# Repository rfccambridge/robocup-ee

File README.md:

## Installing ROS Kinetic
- Follow the steps 1.1 - 1.5 in this guide here: http://wiki.ros.org/kinetic/Installation/Ubuntu

## Build Environment Installation

- Make sure you have clang-format installed: 

        apt-cache search clang-format
        sudo apt-get install clang-format-<version>
    
- `source /opt/ros/kinetic/setup.bash`
- `cd <your robocup directory>/catkin_ws/src`
- `catkin_init_workspace`
- `cd <your robocup directory>/catkin_ws`
- `catkin_make`
- `rosrun using_markers brain`
- `source <your robocup directory>/catkin_ws/devel/setup.bash`

### Persistent Evinvironment Setup
- To have ROS initialized everytime you open a terminal window, simply add the `source` line above to the end of your `~/.bashrc` file.

## Running the Rendered, Simulator and Engine
### Renderer
- `roscore`
- `rosrun rviz rviz`

### Simulator
- `rosrun using_markers simulator`

### Engine
- Make sure running `echo $ROS_PACKAGE_PATH` prints something similar to `/home/<your_user>/catkin_ws/src:/opt/ros/kinetic/share:/opt/ros/kinetic/stacks`

## Setting Up Your Own Branch To Work In

- `git checkout -b <your name>_branch`
- Now, all changes you make will affect only your environment and no one else's.

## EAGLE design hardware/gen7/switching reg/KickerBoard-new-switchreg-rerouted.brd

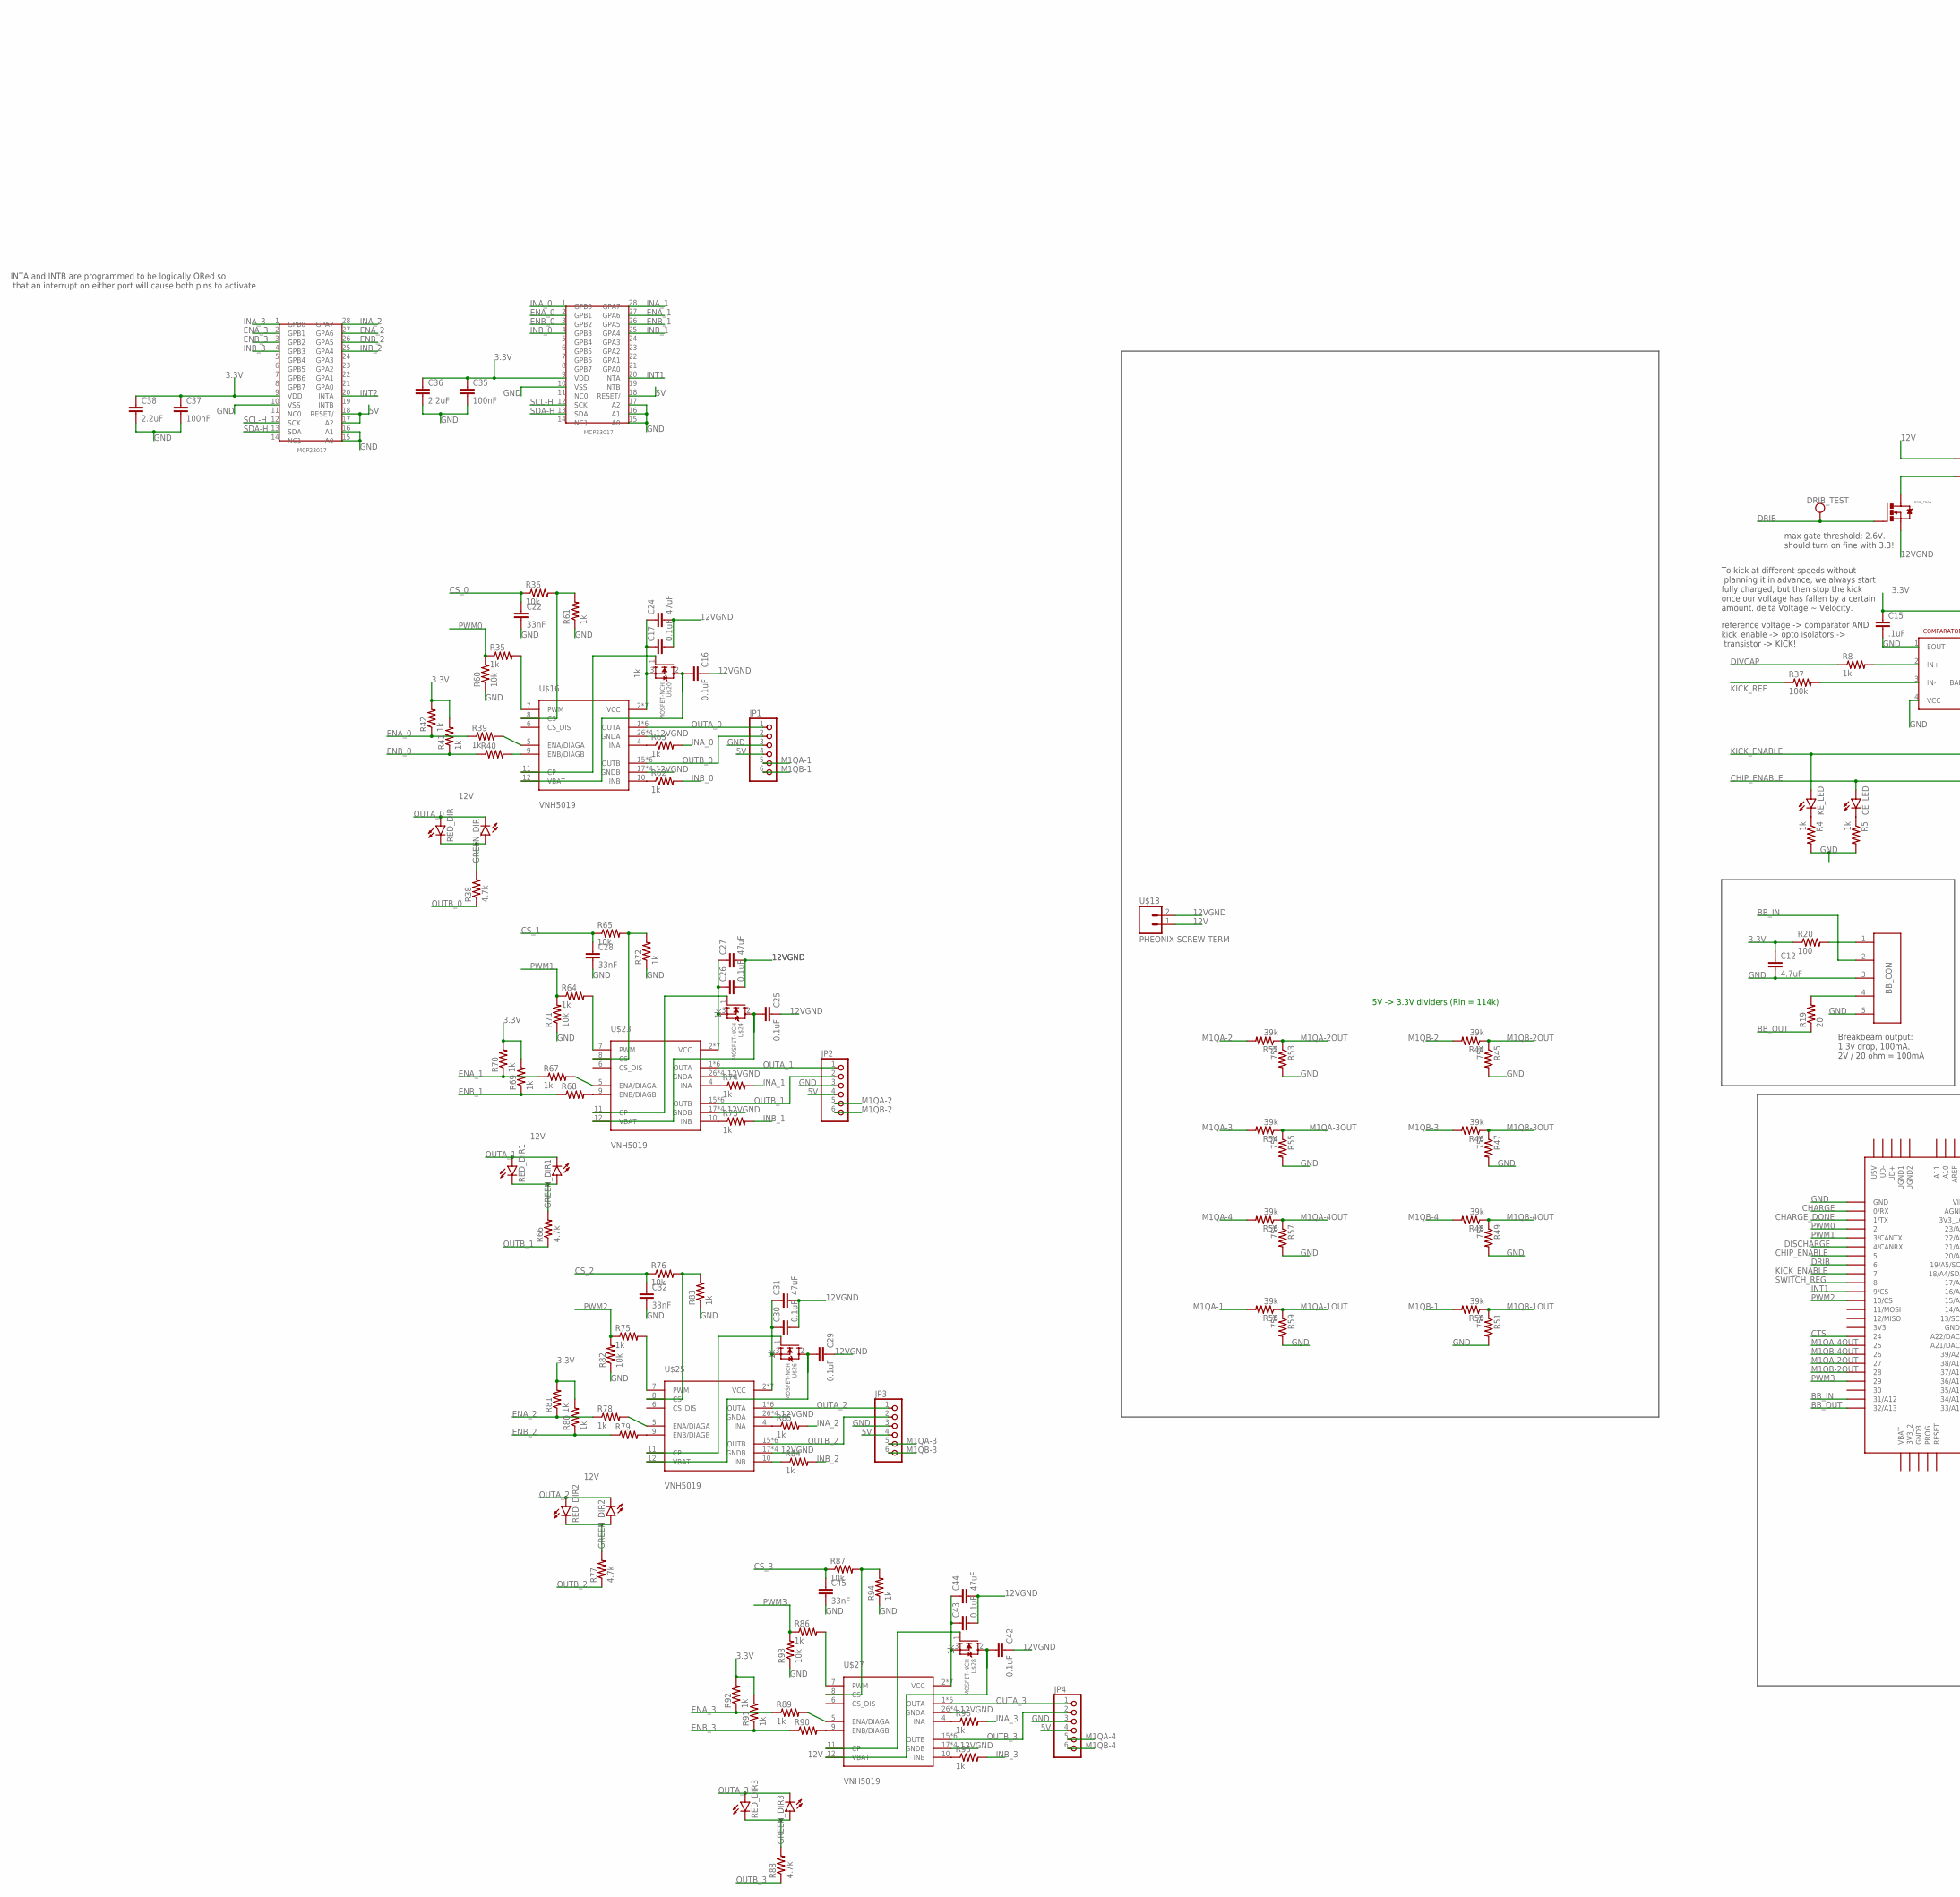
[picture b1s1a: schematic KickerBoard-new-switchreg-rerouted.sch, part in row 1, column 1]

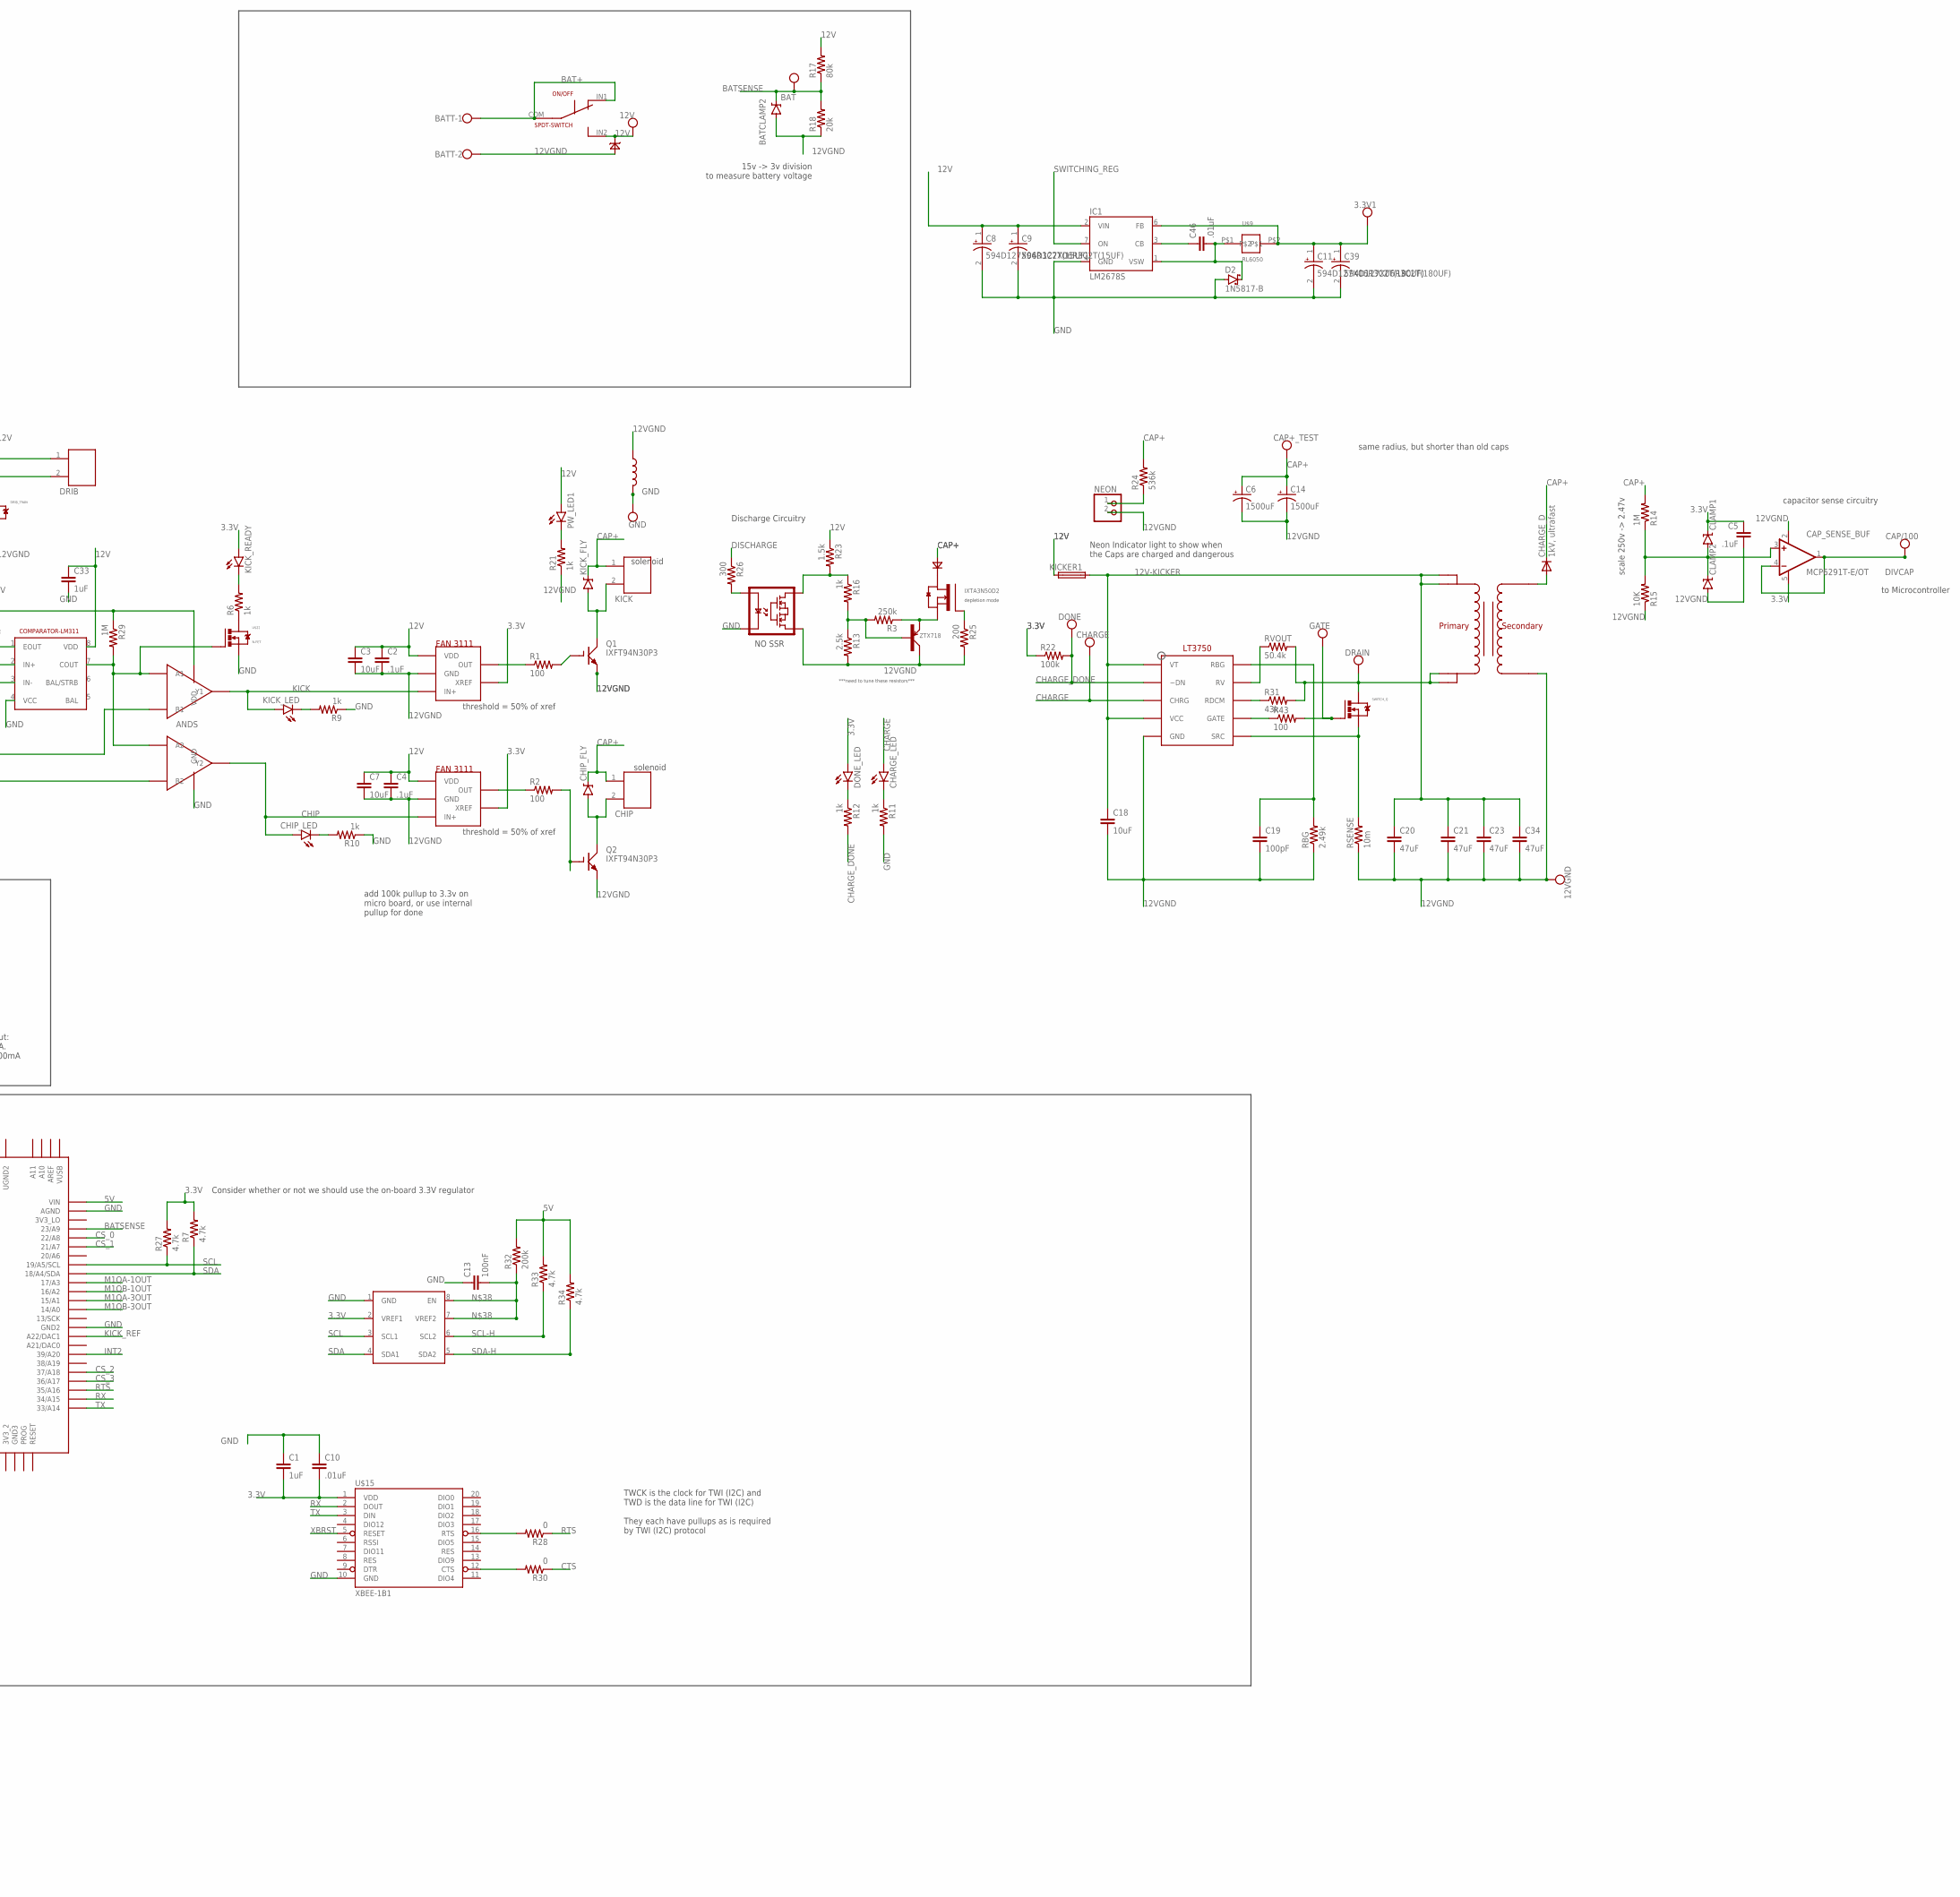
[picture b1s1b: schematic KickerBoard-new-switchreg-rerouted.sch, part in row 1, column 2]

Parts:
3.3V1, 12V, 12VGND: TEST_PT; TESTING_PT
ANDS: AND-DUAL; TSSOP8
BAT: TEST_PT; TESTING_PT
BATCLAMP2: DIODE-ZENERDO214AC; DO214AC
BATT: W237-102
BB_CON: JST-5; JST-5-2MM
C1, C33: 1uF; 1206
C2, C4: .1uF; 1206
C3, C7: 10uF; 1206
C5, C15: .1uF; 0805
C6, C14: 1500uF; EB35D
C8, C9: 594D127X06R3C2T(15UF); CAPCP7132X250N
C10: .01uF; 1206
C11, C39: 594D127X06R3C2T(180UF); CAPCP7132X250N
C12: 4.7uF; 0805
C13, C35, C37: 100nF; 0805
C16, C17, C25, C26, C29, C30, C42, C43: 0.1uF; 0805
C18: 10uF; 0805
C19: 100pF; 0805
C20, C21, C23, C24, C27, C31, C34, C44: 47uF; 1206
C22, C28, C32, C45: 33nF; 0805
C36, C38: 2.2uF; 0805
C46: .01uF; 0805
CAP+_TEST: TEST_PT; TESTING_PT
CAP/100: TEST_PT; TESTING_PT
CAP_SENSE_BUF: MCP6291T-E/OT; SOT23-5
CE_LED: LED1206; LED-1206
CHARGE: TEST_PT; TESTING_PT
CHARGE_D: 1kV, ultrafast; DO214AC
CHARGE_LED: LED1206; LED-1206
CHARGE_U: LT3750; 10-MSOP
CHIP: JST-22MM; JST-2-2MM
CHIP_FLY: DIODE-ZENERDO214AB; DO214AB
CHIP_LED: LED1206; LED-1206
CLAMP1, CLAMP2: DIODE-ZENERDO214AC; DO214AC
D2: 1N5817-B; DO41-7.6
DONE: TEST_PT; TESTING_PT
DONE_LED: LED1206; LED-1206
DRAIN: TEST_PT; TESTING_PT
DRIB: JST-22MM; JST-2-2MM
DRIB_TEST: TEST_PT; TESTING_PT
DRIB_TRAN: N-MOSFETDPAK; DPAK
GATE: TEST_PT; TESTING_PT
GND: TEST_PT; TESTING_PT
GREEN_DIR, GREEN_DIR1, GREEN_DIR2, GREEN_DIR3: LED1206; LED-1206
IC1: LM2678S; TO263-7
JP1, JP2, JP3, JP4: PINHD-1X6; 1X06
KE_LED: LED1206; LED-1206
KICK: JST-22MM; JST-2-2MM
KICKER1: TR5
KICK_FLY: DIODE-ZENERDO214AB; DO214AB
KICK_LED: LED1206; LED-1206
KICK_READY: LED1206; LED-1206
NEON: PINHD-1X2; 1X02
ON/OFF: SPDT-SWITCH; CK_SWITCH
PW_LED1: LED1206; LED-1206
Q1, Q2: IXFT94N30P3; TO268
R1, R2, R20, R43: 100; 0805
R3: 250k; 0805
R4, R5, R6, R8, R9, R10, R11, R12, R16, R21, R35, R39, R40, R41, R42, R61, R62, R63, R64, R67, R68, R69, R70, R72, R73, R74, R75, R78, R79, R80, R81, R83, R84, R85, R86, R89, R90, R91, R92, R94, R95, R96: 1k; 0805
R7, R27, R33, R34, R38, R66, R77, R88: 4.7k; 0805
R13: 2.5k; 0805
R14, R29: 1M; 0805
R15: 10K; 0805
R17: 80k; 0805
R18: 20k; 0805
R19: 20; 0805
R22, R37: 100k; 0805
R23: 1.5k; 0805
R24: 536k; 0805
R25: 200; 0805
R26: 300; 0805
R28, R30: 0; 0805
R31: 43k; 0805
R32: 200k; 0805
R36, R60, R65, R71, R76, R82, R87, R93: 10k; 0805
R44, R46, R48, R50, R52, R54, R56, R58: 39k; 0805
R45, R47, R49, R51, R53, R55, R57, R59: 75k; 0805
RBG: 2.49k; 0805
RED_DIR, RED_DIR1, RED_DIR2, RED_DIR3: LED1206; LED-1206
RSENSE: 10m; R2512
RVOUT: 50.4k; 0805
SWITCH_Q: N-MOSFETDPAK; DPAK
U$1, U$4: FAN31111; SOT23-5
U$2: IXTA3N50D2; TO-263
U$3: 32052-TRANSFORMER; 10-TRANSFORMER
U$5: VO1400AEFTR; SOP4
U$6: ZTX718; TO92
U$7: 1N4007; THROUGH-HOLE-2
U$8: PCA9306; SOIC8
U$9: RL6050
U$12: 13VZENER; THROUGH-HOLE-2
U$13: PHEONIX-SCREW-TERM; 1X02-PHEONIX
U$14: TEENSY_3.5/3.6
U$15: XBEE-1B1; XBEE-1
U$16, U$23, U$25, U$27: VNH5019; MULTIPOWERSO-30
U$17, U$21: IO-EXPANDER; SSOP
U$18: LM311; SOIC8
U$19: INDUCTOR; 0805
U$20, U$24, U$26, U$28: MOSFET-NCH; TO252-3
U$22: N-FET; SOT-23

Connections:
3.3V: ANDS.P$8 (VDD), C1.2, C5.1, C10.2, C12.1, C15.1, C35.1, C36.1, C37.1, C38.1, CAP_SENSE_BUF.5 (V+), CLAMP1.C, DONE_LED.A, KICK_READY.A, R7.2, R20.1, R22.1, R27.2, R29.1, R41.2, R42.2, R69.2, R70.2, R80.2, R81.2, R91.2, R92.2, U$1.4 (XREF), U$4.4 (XREF), U$8.2 (VREF1), U$15.1 (VDD), U$17.9 (VDD), U$21.9 (VDD)
5V: JP1.4, JP2.4, JP3.4, JP4.4, R32.2, R33.2, R34.2, U$14.VIN, U$17.18 (RESET/), U$21.17 (A2), U$21.18 (RESET/)
12V: 12V.P$1, C2.1, C3.1, C4.1, C7.1, C8.1, C9.1, C16.1, C25.1, C29.1, C33.1, C42.1, DRIB.1, IC1.2 (VIN), KICKER1.1, ON/OFF.IN2 (P2), PW_LED1.A, R17.2, R23.1, U$1.1 (VDD), U$4.1 (VDD), U$12.-, U$13.1, U$16.12 (VBAT), U$18.8 (VDD), U$20.2 (D), U$23.12 (VBAT), U$24.2 (D), U$25.12 (VBAT), U$26.2 (D), U$27.12 (VBAT), U$28.2 (D)
12V-KICKER: C18.1, C20.1, C21.1, C23.1, C34.1, CHARGE_U.P$1 (VT), CHARGE_U.P$4 (VCC), KICKER1.2, U$3.P$4, U$3.P$5
12VGND: 12VGND.P$1, BATCLAMP2.A, BATT.2, C2.2, C3.2, C4.2, C5.2, C6.-, C7.2, C14.-, C16.2, C17.2, C18.2, C19.2, C20.2, C21.2, C23.2, C24.2, C25.2, C26.2, C27.2, C29.2, C30.2, C31.2, C34.2, C42.2, C43.2, C44.2, CAP_SENSE_BUF.2 (V-), CHARGE_U.P$5 (GND), CLAMP2.A, DRIB_TRAN.SOURCE (S), NEON.2, Q1.E, Q2.E, R13.2, R15.1, R18.1, R21.1, R25.2, RBG.1, RSENSE.1, U$1.2 (GND), U$3.P$10, U$4.2 (GND), U$5.3 (S2), U$6.LEFT (COLLECTOR), U$12.+, U$13.2, U$16.17 (GNDB), U$16.18 (GNDB), U$16.19 (GNDB), U$16.20 (GNDB), U$16.26 (GNDA), U$16.27 (GNDA), U$16.28 (GNDA), U$16.29 (GNDA), U$19.1, U$23.17 (GNDB), U$23.18 (GNDB), U$23.19 (GNDB), U$23.20 (GNDB), U$23.26 (GNDA), U$23.27 (GNDA), U$23.28 (GNDA), U$23.29 (GNDA), U$25.17 (GNDB), U$25.18 (GNDB), U$25.19 (GNDB), U$25.20 (GNDB), U$25.26 (GNDA), U$25.27 (GNDA), U$25.28 (GNDA), U$25.29 (GNDA), U$27.17 (GNDB), U$27.18 (GNDB), U$27.19 (GNDB), U$27.20 (GNDB), U$27.26 (GNDA), U$27.27 (GNDA), U$27.28 (GNDA), U$27.29 (GNDA)
BAT+: BATT.1, ON/OFF.COM, ON/OFF.IN1 (P1)
BATSENSE: BAT.P$1, BATCLAMP2.C, R17.1, R18.2, U$14.23/A9
BB_IN: BB_CON.2, U$14.31/A12
BB_OUT: R19.1, U$14.32/A13
CAP+: C6.+, C14.+, CAP+_TEST.P$1, CHARGE_D.C, CHIP.1, CHIP_FLY.CATHODE (C), KICK.1, KICK_FLY.CATHODE (C), R14.2, R24.2, U$7.+ (D+)
CHARGE: CHARGE.P$1, CHARGE_LED.A, CHARGE_U.P$3 (CHRG), U$14.0/RX
CHARGE_DONE: CHARGE_U.P$2 (~DN), DONE.P$1, R12.2, R22.2, U$14.1/TX
CHIP: ANDS.P$3 (Y2), CHIP_LED.A, U$1.3 (IN+)
CHIP_ENABLE: ANDS.P$6 (B2), CE_LED.A, U$14.5
COMP_OUT: ANDS.P$1 (A1), ANDS.P$5 (A2), R29.2, U$18.7 (COUT), U$22.G
CS_0: C22.1, R36.1, U$14.22/A8
CS_1: C28.1, R65.1, U$14.21/A7
CS_2: C32.1, R76.1, U$14.37/A18
CS_3: C45.1, R87.1, U$14.36/A17
CTS: R30.1, U$14.24
DISCHARGE: R26.1, U$14.4/CANRX
DIVCAP: CAP/100.P$1, CAP_SENSE_BUF.1 (OUT), CAP_SENSE_BUF.4 (-IN), R8.1
DRIB: DRIB_TEST.P$1, DRIB_TRAN.GATE (G), U$14.6
ENA_0: R39.1, R42.1, U$17.2 (GPB1)
ENA_1: R67.1, R70.1, U$17.27 (GPA6)
ENA_2: R78.1, R81.1, U$21.27 (GPA6)
ENA_3: R89.1, R92.1, U$21.2 (GPB1)
ENB_0: R40.1, R41.1, U$17.3 (GPB2)
ENB_1: R68.1, R69.1, U$17.26 (GPA5)
ENB_2: R79.1, R80.1, U$21.26 (GPA5)
ENB_3: R90.1, R91.1, U$21.3 (GPB2)
GND: ANDS.P$4 (GND), BB_CON.3, BB_CON.5, C1.1, C8.2, C9.2, C10.1, C11.2, C12.2, C13.1, C15.2, C22.2, C28.2, C32.2, C33.2, C35.2, C36.2, C37.2, C38.2, C39.2, C45.2, D2.A, GND.P$1, IC1.4 (GND), JP1.3, JP2.3, JP3.3, JP4.3, R4.2, R5.2, R9.1, R10.1, R11.2, R45.2, R47.2, R49.2, R51.2, R53.2, R55.2, R57.2, R59.2, R60.1, R61.1, R71.1, R72.1, R82.1, R83.1, R93.1, R94.1, U$5.2 (LED-), U$8.1 (GND), U$14.AGND, U$14.GND, U$14.GND2, U$15.10 (GND), U$17.10 (VSS), U$17.15 (A0), U$17.16 (A1), U$17.17 (A2), U$18.1 (EOUT), U$18.4 (VCC), U$19.2, U$21.10 (VSS), U$21.15 (A0), U$21.16 (A1), U$22.S
INA_0: R63.2, U$17.1 (GPB0)
INA_1: R74.2, U$17.28 (GPA7)
INA_2: R85.2, U$21.28 (GPA7)
INA_3: R96.2, U$21.1 (GPB0)
INB_0: R62.2, U$17.4 (GPB3)
INB_1: R73.2, U$17.25 (GPA4)
INB_2: R84.2, U$21.25 (GPA4)
INB_3: R95.2, U$21.4 (GPB3)
INT1: U$14.9/CS, U$17.20 (INTA)
INT2: U$14.39/A20, U$21.20 (INTA)
KICK: ANDS.P$7 (Y1), KICK_LED.A, U$4.3 (IN+)
KICK_ENABLE: ANDS.P$2 (B1), KE_LED.A, U$14.7
KICK_REF: R37.1, U$14.A22/DAC1
LOWCHIP: CHIP.2, CHIP_FLY.ANODE (A), Q2.C@1 (C), Q2.C@2 (C)
LOWKICK: KICK.2, KICK_FLY.ANODE (A), Q1.C@1 (C), Q1.C@2 (C)
M1QA-1: JP1.5, R58.2
M1QA-1OUT: R58.1, R59.1, U$14.17/A3
M1QA-2: JP2.5, R52.2
M1QA-2OUT: R52.1, R53.1, U$14.27
M1QA-3: JP3.5, R54.2
M1QA-3OUT: R54.1, R55.1, U$14.15/A1
M1QA-4: JP4.5, R56.2
M1QA-4OUT: R56.1, R57.1, U$14.25
M1QB-1: JP1.6, R50.2
M1QB-1OUT: R50.1, R51.1, U$14.16/A2
M1QB-2: JP2.6, R44.2
M1QB-2OUT: R44.1, R45.1, U$14.28
M1QB-3: JP3.6, R46.2
M1QB-3OUT: R46.1, R47.1, U$14.14/A0
M1QB-4: JP4.6, R48.2
M1QB-4OUT: R48.1, R49.1, U$14.26
unnamed: DRAIN.P$1, R31.2, RVOUT.2, SWITCH_Q.DRAIN (D), U$3.P$6, U$3.P$7
unnamed: R1.1, U$4.5 (OUT)
unnamed: Q2.G, R2.2
unnamed: R28.2, U$15.16 (RTS)
unnamed: R2.1, U$1.5 (OUT)
unnamed: CHARGE_U.P$8 (RDCM), R31.1
unnamed: C19.1, CHARGE_U.P$10 (RBG), RBG.2
unnamed: Q1.G, R1.2
unnamed: GATE.P$1, R43.2, SWITCH_Q.GATE (G)
unnamed: R3.1, U$2.LOWER_RIGHT (SOURCE), U$6.RIGHT (EMITTER)
unnamed: KE_LED.C, R4.1
unnamed: CHARGE_U.P$9 (RV), RVOUT.1
unnamed: CE_LED.C, R5.1
unnamed: R6.1, U$22.D
unnamed: KICK_LED.C, R9.2
unnamed: R30.2, U$15.12 (CTS)
unnamed: CHIP_LED.C, R10.2
unnamed: R3.2, R13.1, R16.2, U$6.CENTER (BASE)
unnamed: DONE_LED.C, R12.1
unnamed: CHARGE_LED.C, R11.1
unnamed: R25.1, U$2.LOWER_LEFT (GATE)
unnamed: PW_LED1.C, R21.2
unnamed: CHARGE_U.P$6 (SRC), RSENSE.2, SWITCH_Q.SOURCE (S)
unnamed: GREEN_DIR.A, R38.2, RED_DIR.C
unnamed: R36.2, R61.2, U$16.8 (CS)
unnamed: R35.2, U$16.7 (PWM)
unnamed: R39.2, U$16.5 (ENA/DIAGA)
unnamed: R16.1, R23.2, U$5.4 (S1)
unnamed: R26.2, U$5.1 (LED+)
unnamed: R40.2, U$16.9 (ENB/DIAGB)
unnamed: BB_CON.4, R19.2
unnamed: KICK_READY.C, R6.2
unnamed: CHARGE_U.P$7 (GATE), R43.1
unnamed: R8.2, U$18.2 (IN+)
unnamed: U$2.TAB (DRAIN), U$7.- (D-)
unnamed: R62.1, U$16.10 (INB)
unnamed: C13.2, R32.1, U$8.7 (VREF2), U$8.8 (EN)
unnamed: R63.1, U$16.4 (INA)
unnamed: BB_CON.1, R20.2
unnamed: U$16.11 (CP), U$20.1 (G)
unnamed: C17.1, C24.1, U$16.2 (VCC), U$16.3 (VCC), U$16.13 (VCC), U$16.14 (VCC), U$16.23 (VCC), U$16.VCC, U$16.VCC@1 (VCC), U$20.3 (S)
unnamed: GREEN_DIR1.A, R66.2, RED_DIR1.C
unnamed: R65.2, R72.2, U$23.8 (CS)
unnamed: R64.2, U$23.7 (PWM)
unnamed: R67.2, U$23.5 (ENA/DIAGA)
unnamed: R68.2, U$23.9 (ENB/DIAGB)
unnamed: U$23.11 (CP), U$24.1 (G)
unnamed: C26.1, C27.1, U$23.2 (VCC), U$23.3 (VCC), U$23.13 (VCC), U$23.14 (VCC), U$23.23 (VCC), U$23.VCC, U$23.VCC@1 (VCC), U$24.3 (S)
unnamed: R73.1, U$23.10 (INB)
unnamed: R74.1, U$23.4 (INA)
unnamed: GREEN_DIR2.A, R77.2, RED_DIR2.C
unnamed: R76.2, R83.2, U$25.8 (CS)
unnamed: R75.2, U$25.7 (PWM)
unnamed: R78.2, U$25.5 (ENA/DIAGA)
unnamed: R79.2, U$25.9 (ENB/DIAGB)
unnamed: U$25.11 (CP), U$26.1 (G)
unnamed: C30.1, C31.1, U$25.2 (VCC), U$25.3 (VCC), U$25.13 (VCC), U$25.14 (VCC), U$25.23 (VCC), U$25.VCC, U$25.VCC@1 (VCC), U$26.3 (S)
unnamed: R84.1, U$25.10 (INB)
unnamed: R85.1, U$25.4 (INA)
unnamed: GREEN_DIR3.A, R88.2, RED_DIR3.C
unnamed: R87.2, R94.2, U$27.8 (CS)
unnamed: R86.2, U$27.7 (PWM)
unnamed: R89.2, U$27.5 (ENA/DIAGA)
unnamed: R37.2, U$18.3 (IN-)
unnamed: R90.2, U$27.9 (ENB/DIAGB)
unnamed: U$27.11 (CP), U$28.1 (G)
unnamed: C43.1, C44.1, U$27.2 (VCC), U$27.3 (VCC), U$27.13 (VCC), U$27.14 (VCC), U$27.23 (VCC), U$27.VCC, U$27.VCC@1 (VCC), U$28.3 (S)
unnamed: R95.1, U$27.10 (INB)
unnamed: R96.1, U$27.4 (INA)
unnamed: C46.1, IC1.3 (CB)
unnamed: 3.3V1.P$1, C11.1, C39.1, IC1.6 (FB), U$9.P$2
unnamed: C46.2, D2.C, IC1.1 (VSW), U$9.P$1
OUTA_0: GREEN_DIR.C, JP1.1, RED_DIR.A, U$16.1 (OUTA), U$16.24 (OUTA), U$16.25 (OUTA), U$16.30 (OUTA), U$16.OUTA, U$16.OUTA@1 (OUTA)
OUTA_1: GREEN_DIR1.C, JP2.1, RED_DIR1.A, U$23.1 (OUTA), U$23.24 (OUTA), U$23.25 (OUTA), U$23.30 (OUTA), U$23.OUTA, U$23.OUTA@1 (OUTA)
OUTA_2: GREEN_DIR2.C, JP3.1, RED_DIR2.A, U$25.1 (OUTA), U$25.24 (OUTA), U$25.25 (OUTA), U$25.30 (OUTA), U$25.OUTA, U$25.OUTA@1 (OUTA)
OUTA_3: GREEN_DIR3.C, JP4.1, RED_DIR3.A, U$27.1 (OUTA), U$27.24 (OUTA), U$27.25 (OUTA), U$27.30 (OUTA), U$27.OUTA, U$27.OUTA@1 (OUTA)
OUTB_0: JP1.2, R38.1, U$16.15 (OUTB), U$16.16 (OUTB), U$16.21 (OUTB), U$16.22 (OUTB), U$16.OUTB, U$16.OUTB@1 (OUTB)
OUTB_1: JP2.2, R66.1, U$23.15 (OUTB), U$23.16 (OUTB), U$23.21 (OUTB), U$23.22 (OUTB), U$23.OUTB, U$23.OUTB@1 (OUTB)
OUTB_2: JP3.2, R77.1, U$25.15 (OUTB), U$25.16 (OUTB), U$25.21 (OUTB), U$25.22 (OUTB), U$25.OUTB, U$25.OUTB@1 (OUTB)
OUTB_3: JP4.2, R88.1, U$27.15 (OUTB), U$27.16 (OUTB), U$27.21 (OUTB), U$27.22 (OUTB), U$27.OUTB, U$27.OUTB@1 (OUTB)
PWM0: R35.1, R60.2, U$14.2
PWM1: R64.1, R71.2, U$14.3/CANTX
PWM2: R75.1, R82.2, U$14.10/CS
PWM3: R86.1, R93.2, U$14.29
RTS: R28.1, U$14.35/A16
RX: U$14.34/A15, U$15.2 (DOUT)
SCL: R27.1, U$8.3 (SCL1), U$14.19/A5/SCL
SCL-H: R33.1, U$8.6 (SCL2), U$17.12 (SCK), U$21.12 (SCK)
SDA: R7.1, U$8.4 (SDA1), U$14.18/A4/SDA
SDA-H: R34.1, U$8.5 (SDA2), U$17.13 (SDA), U$21.13 (SDA)
SWITCHING_REG: IC1.7 (ON)
SWITCH_REG: U$14.8
TO_DRIB: DRIB.2, DRIB_TRAN.DRAIN (D)
TO_NEON: NEON.1, R24.1
TRANS_OUT: CHARGE_D.A, U$3.P$1
TX: U$14.33/A14, U$15.3 (DIN)
UNBUF_DIVCAP: CAP_SENSE_BUF.3 (+IN), CLAMP1.A, CLAMP2.C, R14.1, R15.2
XBRST: U$15.5 (RESET)

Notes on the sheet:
scale 250v -> 2.47v
To kick at different speeds without planning it in advance, we always start fully charged, but then stop the kick once our voltage has fallen by a certain amount. delta Voltage ~ Velocity.
reference voltage -> comparator AND kick_enable -> opto isolators -> transistor -> KICK!
add 100k pullup to 3.3v on micro board, or use internal pullup for done
Neon Indicator light to show when the Caps are charged and dangerous
to Microcontroller
threshold = 50% of xref
same radius, but shorter than old caps
Discharge Circuitry
capacitor sense circuitry
15v -> 3v division to measure battery voltage
max gate threshold: 2.6V. should turn on fine with 3.3!
Breakbeam output: 1.3v drop, 100mA. 2V / 20 ohm = 100mA
solenoid
IXTA3N50D2
ZTX718
***need to tune these resistors***
depletion mode
NO SSR
TWCK is the clock for TWI (I2C) and TWD is the data line for TWI (I2C) They each have pullups as is required by TWI (I2C) protocol
INTA and INTB are programmed to be logically ORed so that an interrupt on either port will cause both pins to activate
5V -> 3.3V dividers (Rin = 114k)
Consider whether or not we should use the on-board 3.3V regulator

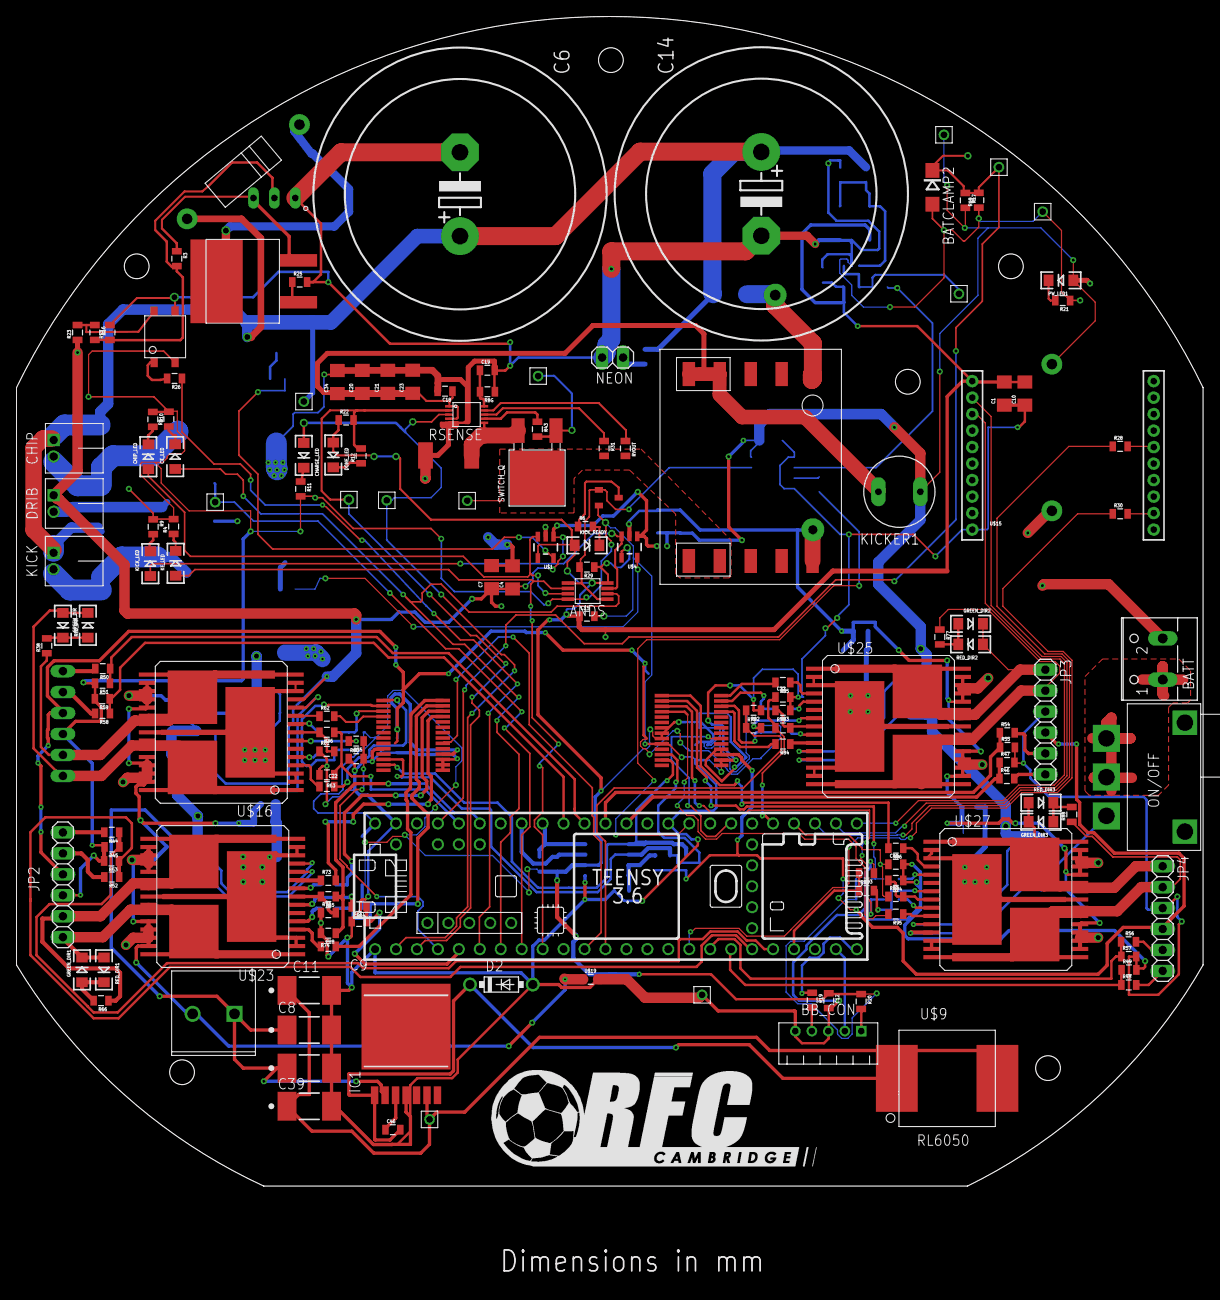
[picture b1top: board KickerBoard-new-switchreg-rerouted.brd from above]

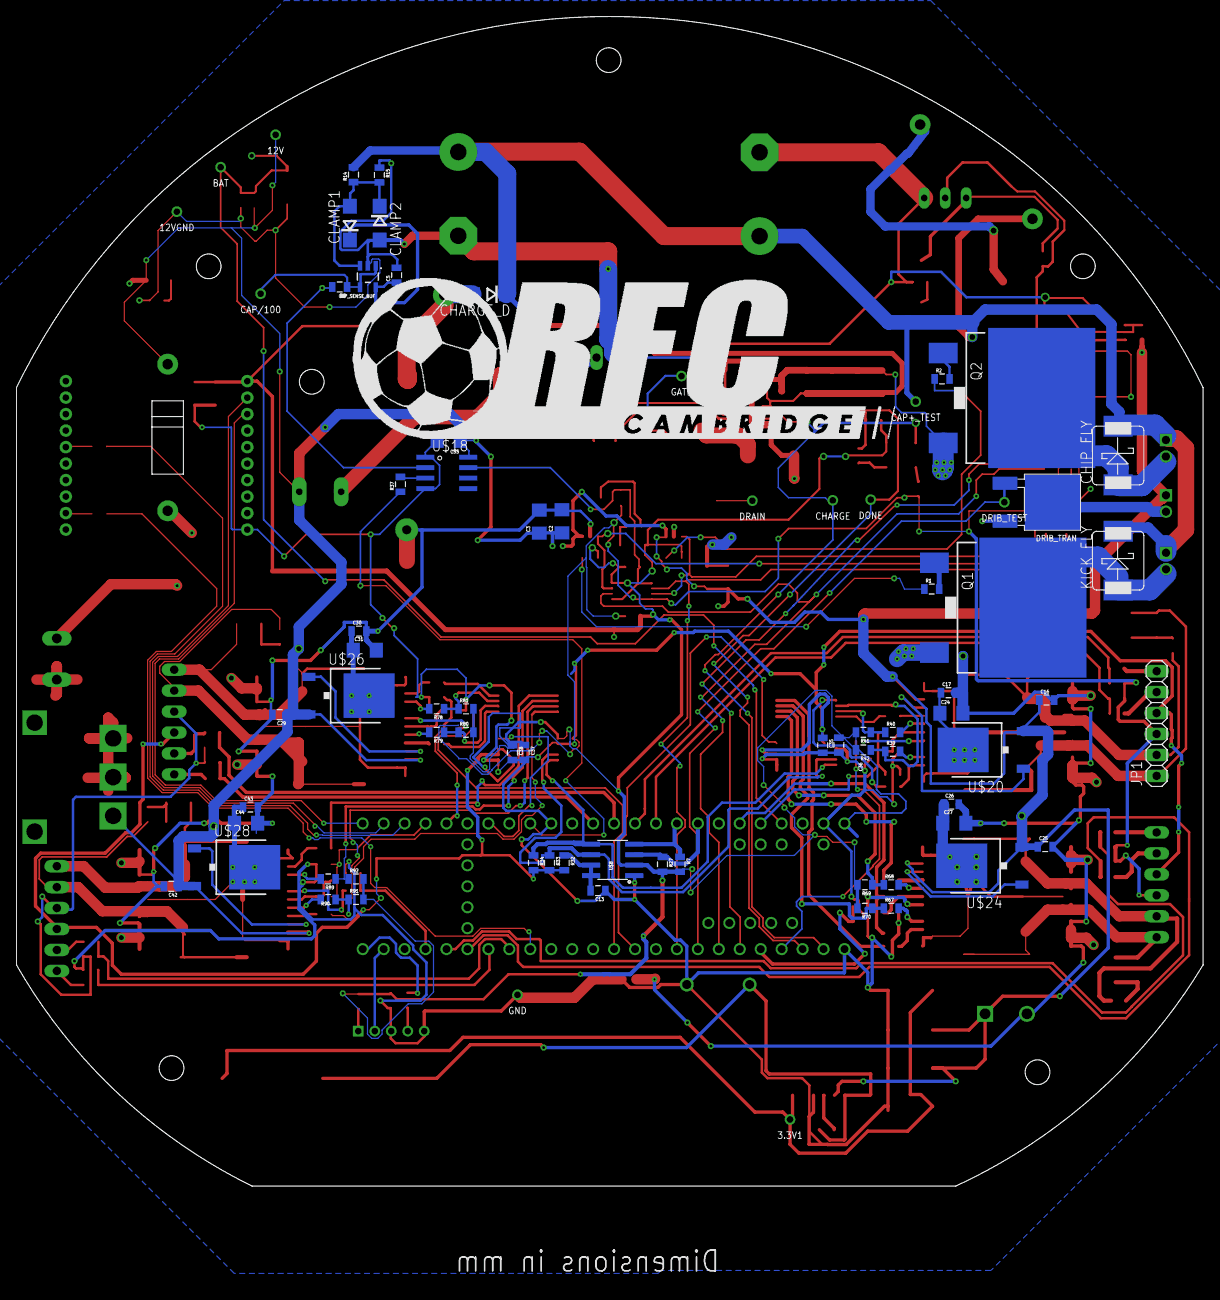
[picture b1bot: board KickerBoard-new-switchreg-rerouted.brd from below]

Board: 2 copper layers, 143.9 x 141.8 mm, 224 parts (66 on the bottom side), 158 nets.

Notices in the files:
parts and their libraries:
SparkFun-Aesthetics: Licensing: Creative Commons ShareAlike 4.0 International - https://creativecommons.org/licenses/by-sa/4.0
SparkFun-Aesthetics: Released under the Creative Commons Attribution Share-Alike 4.0 License
SparkFun-Aesthetics: https://creativecommons.org/licenses/by-sa/4.0
